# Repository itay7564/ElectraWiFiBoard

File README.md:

# ElectraWiFiBoard

A PCB which enables connecting an Electra air conditioner to internet using a Wemos D1 mini esp8266 module

The circuit is based on the [ElectraWiFi](https://github.com/giladger/ElectraWifi) repository by [giladger](https://github.com/giladger) which contains code for this project

I designed it using KiCad

# Bill of Materials
Connector - J1 - 8 pin DIN connector [footprint from CUI MD-80SM](https://www.cuidevices.com/product/interconnect/connectors/din-connectors/md-80sm)

WiFi Module - U1 - WeMos D1 mini

LED - D1-D4 - 3mm pth LED

IR Reciever - U2 - TSOP41xx

Buzzer - BZ1 - 12mm buzzer

Resistor - R4 - PTH resistor 100 ohm

Resistors - R1-R3 - PTH resistor 1K ohm

# Photos

# Credits

Thanks to Guy Eshel who prompted the design and helped with measurments 

Thanks to [giladger](https://github.com/giladger) and the contributors of the [ElectraWiFi](https://github.com/giladger/ElectraWifi) repo which contains the code for this project

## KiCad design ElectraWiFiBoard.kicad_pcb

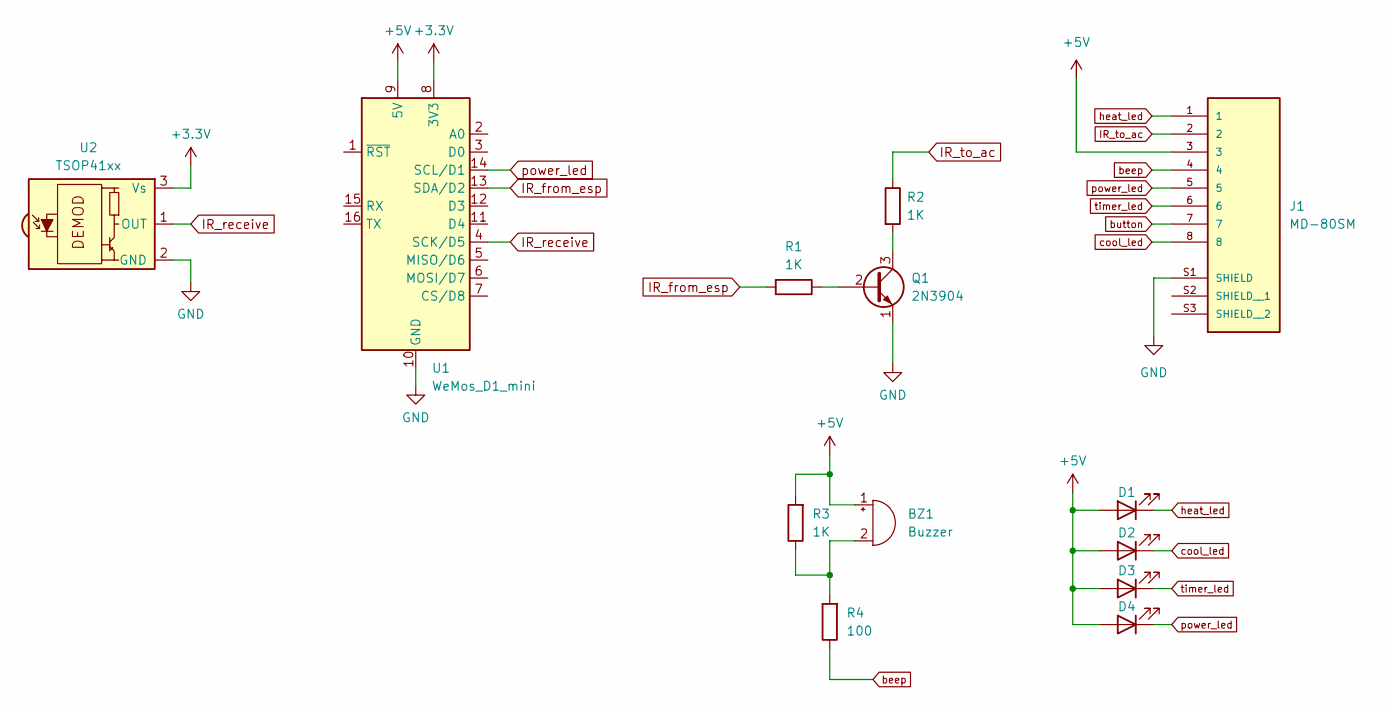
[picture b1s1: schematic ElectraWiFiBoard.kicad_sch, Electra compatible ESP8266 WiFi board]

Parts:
BZ1: Buzzer; Buzzer_12x9.5RM7.6
D1: HEAT; LED_D3.0mm
D2: COOL; LED_D3.0mm
D3: TIMER; LED_D3.0mm
D4: POWER; LED_D3.0mm
J1: MD-80SM; CUI_MD-80SM; PARTREV 02/18/2022
Q1: 2N3904; TO-92_Inline
R1, R2, R3: 1K; R_Axial_DIN0207_L6.3mm_D2.5mm_P7.62mm_Horizontal
R4: 100; R_Axial_DIN0207_L6.3mm_D2.5mm_P7.62mm_Horizontal
U1: WeMos_D1_mini; WEMOS_D1_mini_light
U2: TSOP41xx; Vishay_MOLD-3Pin

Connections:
+3.3V: U1.8 (3V3), U2.3 (Vs)
+5V: BZ1.1 (-), D1.2 (A), D2.2 (A), D3.2 (A), D4.2 (A), J1.3, R3.2, U1.9 (5V)
GND: J1.S1 (SHIELD), Q1.1 (E), U1.10 (GND), U2.2 (GND)
IR_from_esp: R1.2, U1.13 (SDA/D2)
IR_receive: U1.4 (SCK/D5), U2.1 (OUT)
IR_to_ac: J1.2, R2.1
unnamed: BZ1.2 (+), R3.1, R4.2
unnamed: Q1.2 (B), R1.1
unnamed: Q1.3 (C), R2.2
beep: J1.4, R4.1
button: J1.7
cool_led: D2.1 (K), J1.8
heat_led: D1.1 (K), J1.1
power_led: D4.1 (K), J1.5, U1.14 (SCL/D1)
timer_led: D3.1 (K), J1.6

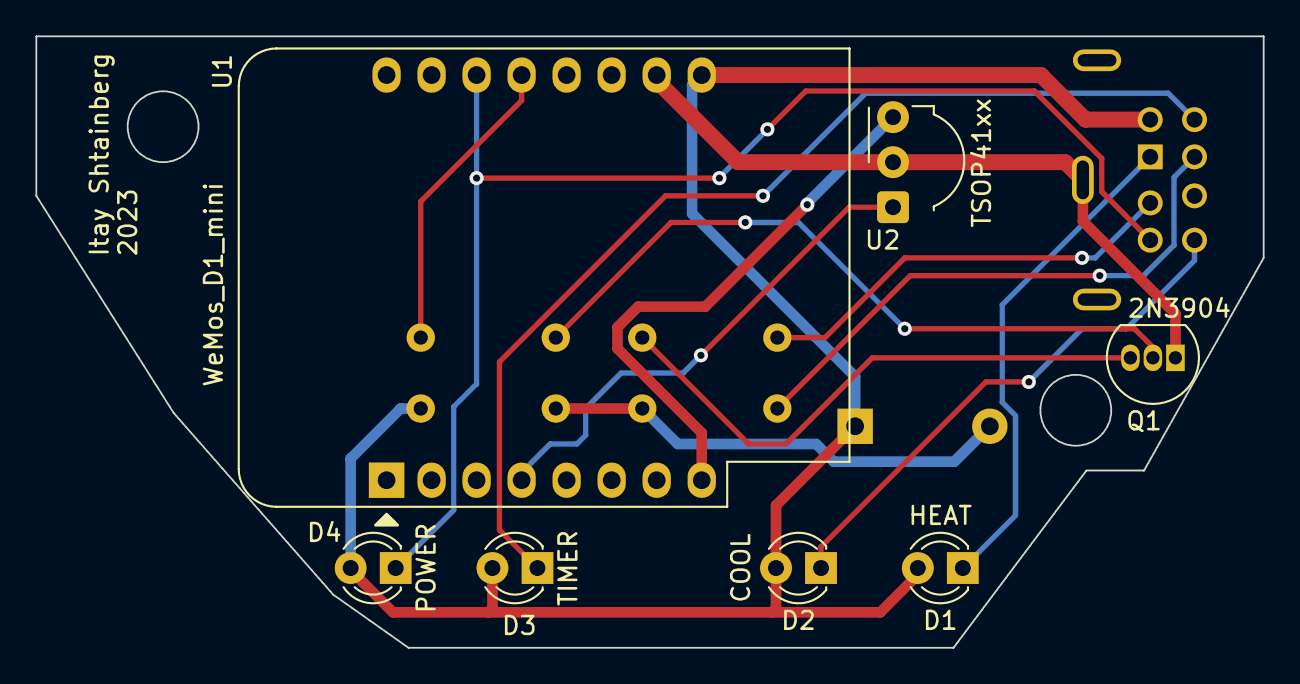
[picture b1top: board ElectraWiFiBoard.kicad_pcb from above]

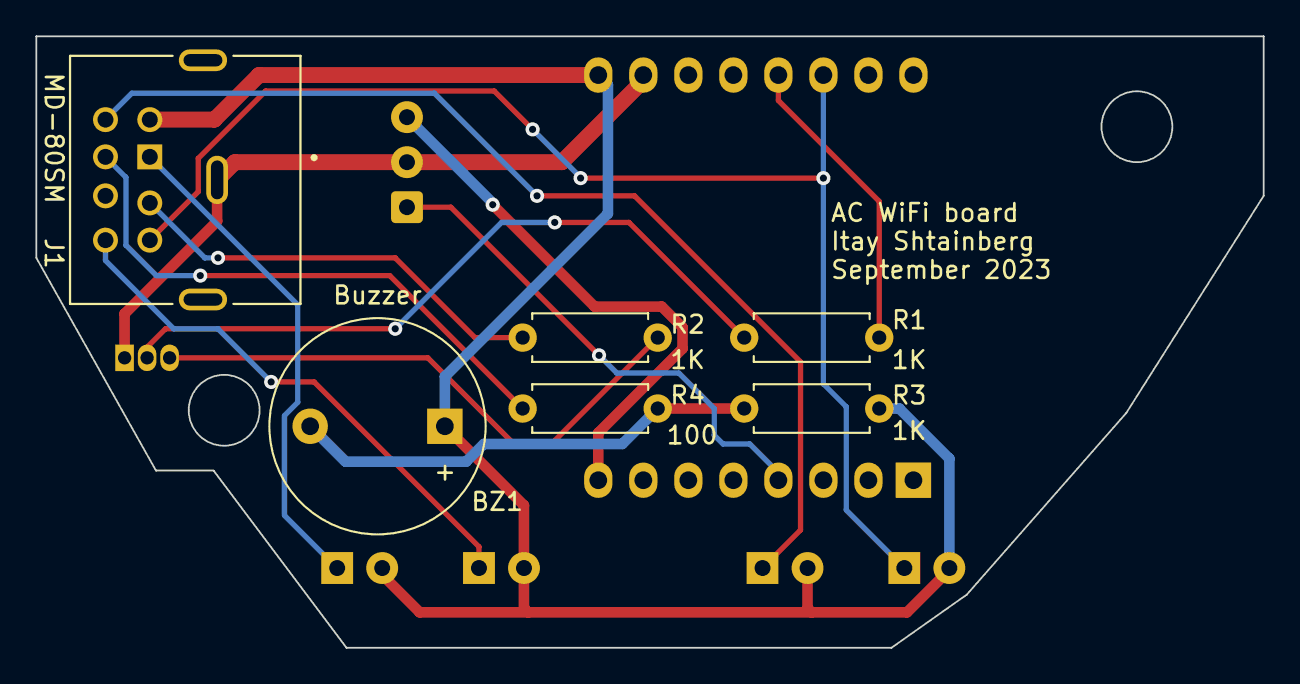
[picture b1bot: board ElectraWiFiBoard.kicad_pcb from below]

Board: 2 copper layers, 69.2 x 34.5 mm, 13 parts (6 on the bottom side), 14 nets.

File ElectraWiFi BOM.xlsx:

Id | Designator | Footprint | Quantity | Designation | Supplier and ref
1 | J1 | CUI_MD-80SM | 1 | MD-80SM
2 | U1 | WEMOS_D1_mini_light | 1 | WeMos_D1_mini
3 | D2 | LED_D3.0mm | 1 | COOL
4 | Q1 | TO-92_Inline | 1 | 2N3904
5 | U2 | Vishay_MOLD-3Pin | 1 | TSOP41xx
6 | D3 | LED_D3.0mm | 1 | TIMER
7 | D1 | LED_D3.0mm | 1 | HEAT
8 | D4 | LED_D3.0mm | 1 | POWER
9 | BZ1 | Buzzer_12x9.5RM7.6 | 1 | Buzzer
10 | R4 | R_Axial_DIN0207_L6.3mm_D2.5mm_P7.62mm_Horizontal | 1 | 100
11 | R2,R1,R3 | R_Axial_DIN0207_L6.3mm_D2.5mm_P7.62mm_Horizontal | 3 | 1K

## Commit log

2023-09-16 init commit
2023-09-16 remove gerbers
2023-09-16 remove untracked files
2023-09-16 Add photos
2023-09-16 Remove untracked
2023-09-16 Create LICENSE
